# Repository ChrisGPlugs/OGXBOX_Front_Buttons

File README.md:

Orginal Xbox Front button board. 
Recreated in KiCad based off the Board design of the Gerbers from Thomas Heath
Track Layout redesigned to be almost the same as stock on the back.
All graphics replaced and outline adjusted with curves.

Three options are uploaded.
1. Has the HDD and LAN leds added to it with locations to add resistors. These are 0603 SMD's 
2. Is same as stock with the Tracks on the back.
3. Same as stock but with the layers swapped so the tracks are on the front for if you are worried about tracks getting exposed and shorting things out.

I've done a drawing to make a self adhesive vinyl sticker. This is to be affixed to the back so that it is the same as stock. 
I have not found a suitable suplier yet. 

if I cannot get stickers I will probably use 50mm wide PVC tape on the back of mine and then cut it out with a craft knife or exacto blade

These Tactile switches have the correct measurements. Tact Button Switch 6x6x4.3mm
https://www.mouser.co.uk/ProductDetail/Omron-Electronics/B3F-1000?qs=lK7M36XCk6JQHckSc1xIsg%3D%3D
https://www.digikey.co.uk/en/products/detail/omron-electronics-inc-emc-div/B3F-1000/33150

The connector that plugs into the motherboard is JST PHD 2mm 10 way connector. https://www.jst.co.uk/productSeries.php?pid=88&cat=30
I bought some of these off ali express. You could solder them on directly or use another suitable connector.
https://www.aliexpress.com/item/1005005940137789.html?spm=a2g0o.order_list.order_list_main.17.1e5b1802rfvPIm

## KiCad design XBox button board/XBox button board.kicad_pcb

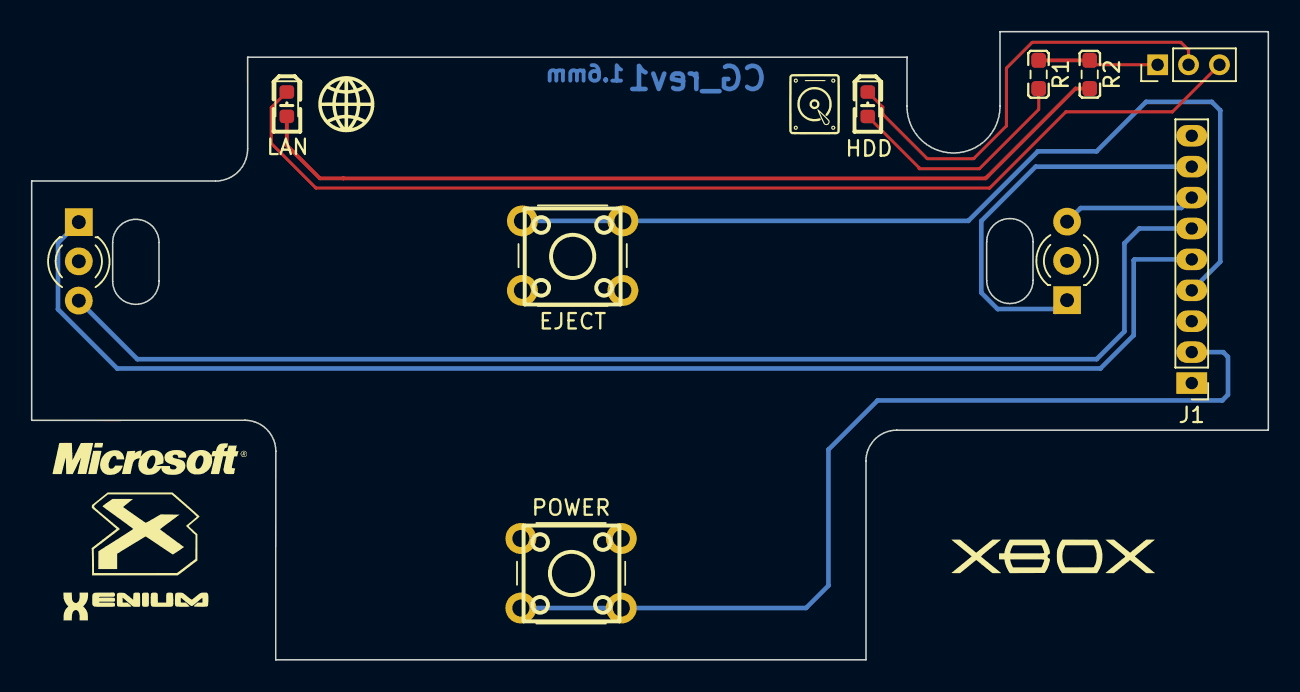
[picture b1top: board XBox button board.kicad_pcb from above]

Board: 2 copper layers, 80.0 x 40.6 mm, 11 parts (0 on the bottom side), 12 nets.

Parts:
D1: LED_Dual_AKA - LEFT; LED_D3.0mm-3
D2: LED_Dual_AKA - Right; LED_D3.0mm-3
EJECT: SW_Push-EJECT; SW_PUSH_6mm_H4.3mm
G: LOGO
HDD_LED1: Blue_56mcd_0603; LED_0603_1608Metric
J1: Conn_01x09_Pin; PinHeader_1x09_P2.00mm_Vertical
J2: Conn_01x03; PinHeader_1x03_P2.00mm_Vertical
LAN_LED1: Red_100mcd_0603; LED_0603_1608Metric
POWER: SW_Push Power; SW_PUSH_6mm_H4.3mm
R1, R2: 100_0603; R_0603_1608Metric_Pad0.98x0.95mm_HandSolder

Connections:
GND: D1.2 (K), D2.2 (K), EJECT.1, J1.1, J1.3, POWER.1
unnamed: D1.1 (A1), J1.5
unnamed: D1.3 (A2), J1.6
unnamed: D2.1 (A1), J1.8
unnamed: D2.3 (A2), J1.7
unnamed: HDD_LED1.2 (A), R1.2
unnamed: HDD_LED1.1 (C), J2.2
unnamed: J1.2, POWER.2
unnamed: EJECT.2, J1.4
unnamed: J2.1, R1.1, R2.1
unnamed: J2.3, LAN_LED1.1 (C)
unnamed: LAN_LED1.2 (A), R2.2

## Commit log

2024-07-06 First rev of board
    First rev of board with HDD and LAN led
2024-07-06 Cut Lines healed
    PCB was showing the cut lines a bit strangely on the preview. Healed the lines and all seems ok now
2024-07-06 NO HDD and LAN Leds
    removed the HDD and Lan LEDs
2024-07-06 Renders of the two boards
    A coupe of pics for reference
2024-07-06 Stock Board added with all tracks on the front
    Did another Variant that has the tracks on the front only to prevent short circuits if tracks are scratched and exposed
2024-08-05 Minor image adjustment
    moved some graphics
2024-08-05 Added Zips of the gerbers
    zipped the gerbers for easy download
2024-08-05 SVG for Rear sticker
    SVG and PDGF of proposed rear sticker
2024-08-22 updated silkscreens
    removed logos from silk print area
2024-08-22 update image
    new image of no lan
